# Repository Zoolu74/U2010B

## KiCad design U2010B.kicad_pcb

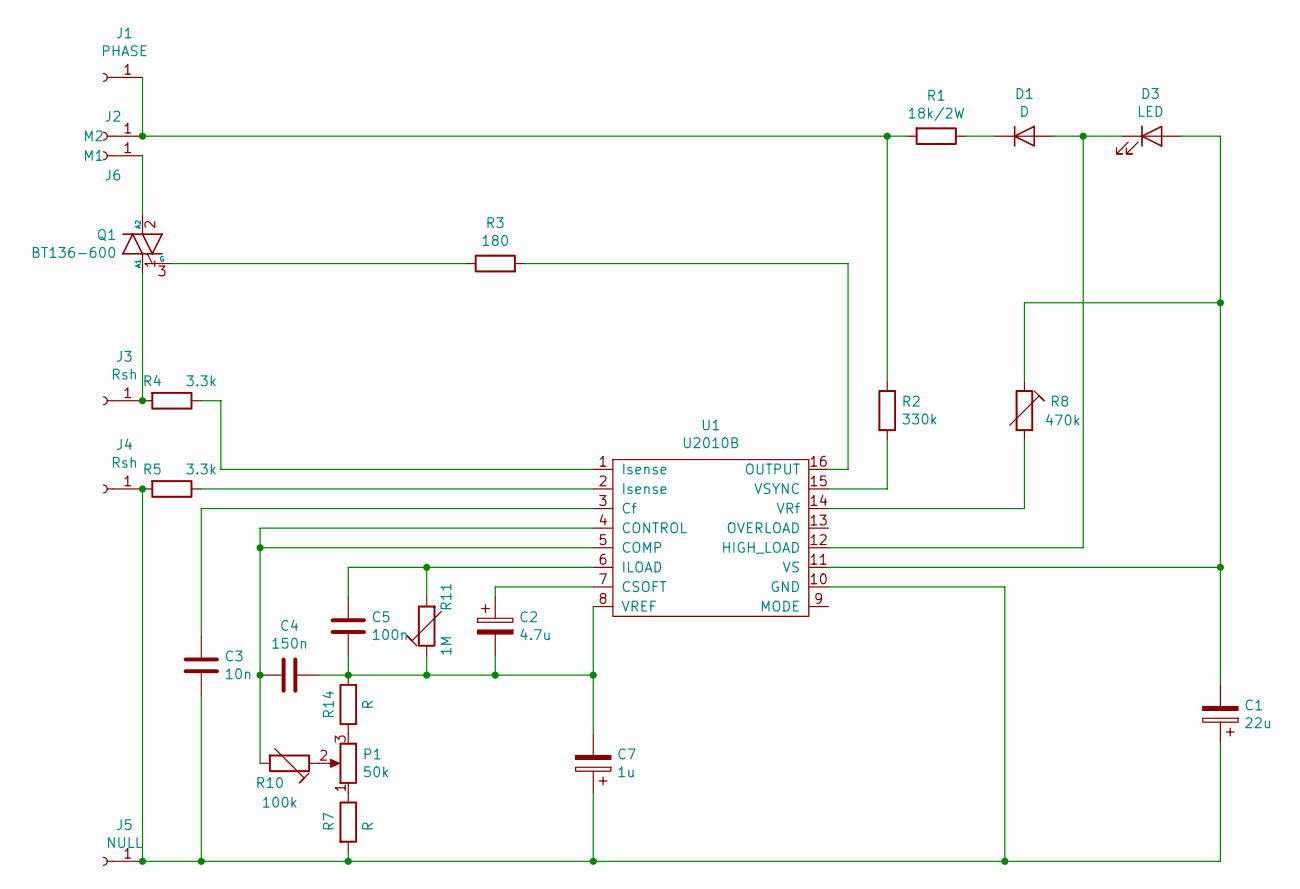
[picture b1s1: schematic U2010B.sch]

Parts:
C1: 22u; CP_Radial_D10.0mm_P3.80mm
C2: 4.7u; CP_Radial_D8.0mm_P3.80mm
C3: 10n; C_0805_2012Metric
C4: 150n; C_0805_2012Metric
C5: 100n; C_0805_2012Metric
C7: 1u; CP_Radial_D8.0mm_P3.80mm
D1: D; D_SMB
D3: LED; LED_D5.0mm
J1: PHASE; SolderWirePad_1x01_Drill2mm
J2: M2; SolderWirePad_1x01_Drill2mm
J3, J4: Rsh; SolderWirePad_1x01_Drill2mm
J5: NULL; SolderWirePad_1x01_Drill2mm
J6: M1; SolderWirePad_1x01_Drill2mm
P1: 50k; Potentiometer_Vishay_248GJ-249GJ_Single_Vertical
Q1: BT136-600; TO-220-3_Vertical
R1: 18k/2W; R_Axial_DIN0414_L11.9mm_D4.5mm_P20.32mm_Horizontal
R2: 330k; R_0805_2012Metric
R3: 180; R_0805_2012Metric
R4, R5: 3.3k; R_0805_2012Metric
R7, R14: R; R_0805_2012Metric
R8: 470k; Potentiometer_Bourns_3339P_Vertical_HandSoldering
R10: 100k; Potentiometer_Bourns_3339P_Vertical_HandSoldering
R11: 1M; Potentiometer_Bourns_3339P_Vertical_HandSoldering
U1: U2010B; SOIC-16_4.55x10.3mm_P1.27mm

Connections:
unnamed: C1.1, C3.2, C7.1, J4.1, J5.1, R5.2, R7.2, U1.10 (GND)
unnamed: C1.2, D3.2 (A), R8.1, U1.11 (VS)
unnamed: C2.1, U1.7 (CSOFT)
unnamed: C2.2, C4.1, C5.1, C7.2, R11.1, R14.2, U1.8 (VREF)
unnamed: C3.1, U1.3 (Cf)
unnamed: C4.2, R10.2, U1.4 (CONTROL), U1.5 (COMP)
unnamed: C5.2, R11.2, U1.6 (ILOAD)
unnamed: D1.1 (K), R1.1
unnamed: D1.2 (A), D3.1 (K), U1.12 (HIGH_LOAD)
unnamed: J1.1, J2.1, R1.2, R2.1
unnamed: J3.1, Q1.1 (A1), R4.2
unnamed: J6.1, Q1.2 (A2)
unnamed: P1.1, R7.1
unnamed: P1.2, R10.1
unnamed: P1.3, R14.1
unnamed: Q1.3 (G), R3.1
unnamed: R2.2, U1.15 (VSYNC)
unnamed: R3.2, U1.16 (OUTPUT)
unnamed: R4.1, U1.1 (Isense)
unnamed: R5.1, U1.2 (Isense)
unnamed: R8.2, U1.14 (VRf)

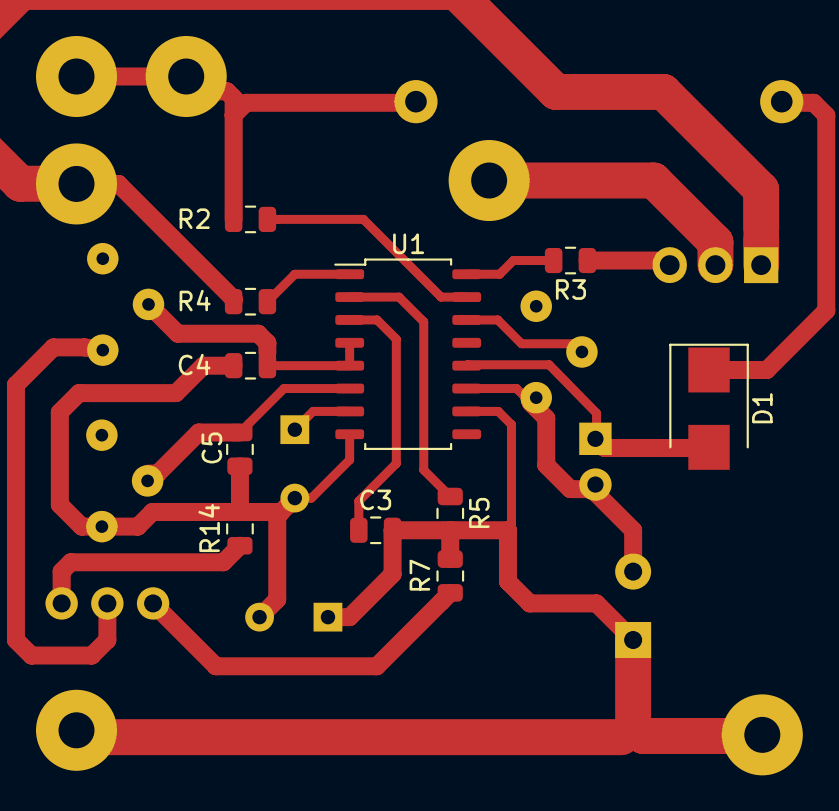
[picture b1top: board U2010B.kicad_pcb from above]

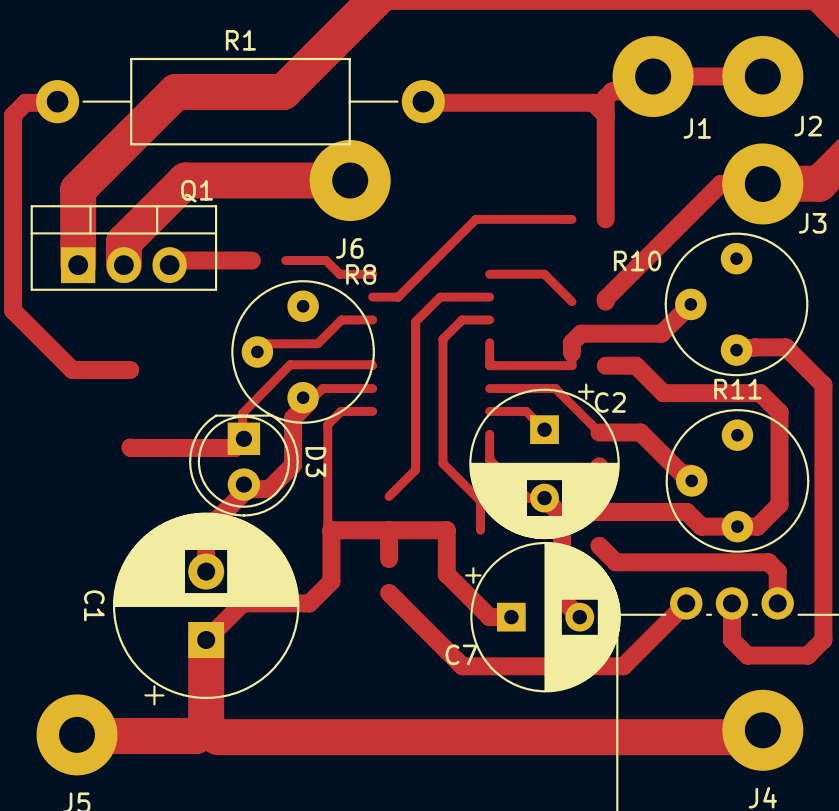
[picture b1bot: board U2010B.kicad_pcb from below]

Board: 2 copper layers, 27 parts (16 on the bottom side), 21 nets.

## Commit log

2020-04-24 Init commit
2020-04-24 Trace PCB
2020-05-01 Add netlist, change some pins for drill.
